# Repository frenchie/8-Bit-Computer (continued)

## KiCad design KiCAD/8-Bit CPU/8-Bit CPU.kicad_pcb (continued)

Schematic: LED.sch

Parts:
D96, D97, D98, D99, D100, D101, D102, D103: LED; LED_0805_2012Metric
RN31, RN32: 1k; R_Array_Concave_4x0603

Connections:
/Control/I0: RN31.5 (R4.2); also elsewhere on the board
/Control/I1: RN31.6 (R3.2); also elsewhere on the board
/Control/I2: RN31.7 (R2.2); also elsewhere on the board
/Control/I3: RN31.8 (R1.2); also elsewhere on the board
/Control/I4: RN32.5 (R4.2); also elsewhere on the board
/Control/I5: RN32.6 (R3.2); also elsewhere on the board
/Control/I6: RN32.7 (R2.2); also elsewhere on the board
/Control/I7: RN32.8 (R1.2); also elsewhere on the board
GND: D96.1 (K), D97.1 (K), D98.1 (K), D99.1 (K), D100.1 (K), D101.1 (K), D102.1 (K), D103.1 (K); also elsewhere on the board
unnamed: D96.2 (A), RN31.4 (R4.1)
unnamed: D97.2 (A), RN31.3 (R3.1)
unnamed: D98.2 (A), RN31.2 (R2.1)
unnamed: D99.2 (A), RN31.1 (R1.1)
unnamed: D100.2 (A), RN32.4 (R4.1)
unnamed: D101.2 (A), RN32.3 (R3.1)
unnamed: D102.2 (A), RN32.2 (R2.1)
unnamed: D103.2 (A), RN32.1 (R1.1)

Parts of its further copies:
D4, D5, D6, D7, D8, D9, D10, D11, D15, D16, D17, D18, D19, D20, D21, D22, D24, D25, D26, D27, D28, D29, D30, D31, D52, D53, D54, D55, D56, D57, D58, D59, D60, D61, D62, D63, D64, D65, D66, D67: LED; LED_0805_2012Metric
RN1, RN2, RN3, RN4, RN13, RN14, RN22, RN23, RN24, RN25: 1k; R_Array_Concave_4x0603

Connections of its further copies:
/ALU/B0: RN22.8 (R1.2); also elsewhere on the board
/ALU/B1: RN22.7 (R2.2); also elsewhere on the board
/ALU/B2: RN22.6 (R3.2); also elsewhere on the board
/ALU/B3: RN22.5 (R4.2); also elsewhere on the board
/ALU/B4: RN23.8 (R1.2); also elsewhere on the board
/ALU/B5: RN23.7 (R2.2); also elsewhere on the board
/ALU/B6: RN23.6 (R3.2); also elsewhere on the board
/ALU/B7: RN23.5 (R4.2); also elsewhere on the board
/ALU/PD0: RN24.8 (R1.2); also elsewhere on the board
/ALU/PD1: RN24.7 (R2.2); also elsewhere on the board
/ALU/PD2: RN24.6 (R3.2); also elsewhere on the board
/ALU/PD3: RN24.5 (R4.2); also elsewhere on the board
/ALU/PD4: RN25.8 (R1.2); also elsewhere on the board
/ALU/PD5: RN25.7 (R2.2); also elsewhere on the board
/ALU/PD6: RN25.6 (R3.2); also elsewhere on the board
/ALU/PD7: RN25.5 (R4.2); also elsewhere on the board
/Program Counter/PC0: RN1.8 (R1.2); also elsewhere on the board
/Program Counter/PC1: RN1.7 (R2.2); also elsewhere on the board
/Program Counter/PC2: RN1.6 (R3.2); also elsewhere on the board
/Program Counter/PC3: RN1.5 (R4.2); also elsewhere on the board
/Program Counter/PC4: RN2.8 (R1.2); also elsewhere on the board
/Program Counter/PC5: RN2.7 (R2.2); also elsewhere on the board
/Program Counter/PC6: RN2.6 (R3.2); also elsewhere on the board
/Program Counter/PC7: RN2.5 (R4.2); also elsewhere on the board
/RAM/MA0: RN3.8 (R1.2); also elsewhere on the board
/RAM/MA1: RN3.7 (R2.2); also elsewhere on the board
/RAM/MA2: RN3.6 (R3.2); also elsewhere on the board
/RAM/MA3: RN3.5 (R4.2); also elsewhere on the board
/RAM/MA4: RN4.8 (R1.2); also elsewhere on the board
/RAM/MA5: RN4.7 (R2.2); also elsewhere on the board
/RAM/MA6: RN4.6 (R3.2); also elsewhere on the board
/RAM/MA7: RN4.5 (R4.2); also elsewhere on the board
/RAM/RAM0: RN13.8 (R1.2); also elsewhere on the board
/RAM/RAM1: RN13.7 (R2.2); also elsewhere on the board
/RAM/RAM2: RN13.6 (R3.2); also elsewhere on the board
/RAM/RAM3: RN13.5 (R4.2); also elsewhere on the board
/RAM/RAM4: RN14.8 (R1.2); also elsewhere on the board
/RAM/RAM5: RN14.7 (R2.2); also elsewhere on the board
/RAM/RAM6: RN14.6 (R3.2); also elsewhere on the board
/RAM/RAM7: RN14.5 (R4.2); also elsewhere on the board
GND: D4.1 (K), D5.1 (K), D6.1 (K), D7.1 (K), D8.1 (K), D9.1 (K), D10.1 (K), D11.1 (K), D15.1 (K), D16.1 (K), D17.1 (K), D18.1 (K), D19.1 (K), D20.1 (K), D21.1 (K), D22.1 (K), D24.1 (K), D25.1 (K), D26.1 (K), D27.1 (K), D28.1 (K), D29.1 (K), D30.1 (K), D31.1 (K), D52.1 (K), D53.1 (K), D54.1 (K), D55.1 (K), D56.1 (K), D57.1 (K), D58.1 (K), D59.1 (K), D60.1 (K), D61.1 (K), D62.1 (K), D63.1 (K), D64.1 (K), D65.1 (K), D66.1 (K), D67.1 (K); also elsewhere on the board
unnamed: D4.2 (A), RN1.4 (R4.1)
unnamed: D5.2 (A), RN1.3 (R3.1)
unnamed: D6.2 (A), RN1.2 (R2.1)
unnamed: D7.2 (A), RN1.1 (R1.1)
unnamed: D8.2 (A), RN2.4 (R4.1)
unnamed: D9.2 (A), RN2.3 (R3.1)
unnamed: D10.2 (A), RN2.2 (R2.1)
unnamed: D11.2 (A), RN2.1 (R1.1)
unnamed: D15.2 (A), RN3.4 (R4.1)
unnamed: D16.2 (A), RN3.3 (R3.1)
unnamed: D17.2 (A), RN3.2 (R2.1)
unnamed: D18.2 (A), RN3.1 (R1.1)
unnamed: D19.2 (A), RN4.4 (R4.1)
unnamed: D20.2 (A), RN4.3 (R3.1)
unnamed: D21.2 (A), RN4.2 (R2.1)
unnamed: D22.2 (A), RN4.1 (R1.1)
unnamed: D24.2 (A), RN13.4 (R4.1)
unnamed: D25.2 (A), RN13.3 (R3.1)
unnamed: D26.2 (A), RN13.2 (R2.1)
unnamed: D27.2 (A), RN13.1 (R1.1)
unnamed: D28.2 (A), RN14.4 (R4.1)
unnamed: D29.2 (A), RN14.3 (R3.1)
unnamed: D30.2 (A), RN14.2 (R2.1)
unnamed: D31.2 (A), RN14.1 (R1.1)
unnamed: D52.2 (A), RN22.4 (R4.1)
unnamed: D53.2 (A), RN22.3 (R3.1)
unnamed: D54.2 (A), RN22.2 (R2.1)
unnamed: D55.2 (A), RN22.1 (R1.1)
unnamed: D56.2 (A), RN23.4 (R4.1)
unnamed: D57.2 (A), RN23.3 (R3.1)
unnamed: D58.2 (A), RN23.2 (R2.1)
unnamed: D59.2 (A), RN23.1 (R1.1)
unnamed: D60.2 (A), RN24.4 (R4.1)
unnamed: D61.2 (A), RN24.3 (R3.1)
unnamed: D62.2 (A), RN24.2 (R2.1)
unnamed: D63.2 (A), RN24.1 (R1.1)
unnamed: D64.2 (A), RN25.4 (R4.1)
unnamed: D65.2 (A), RN25.3 (R3.1)
unnamed: D66.2 (A), RN25.2 (R2.1)
unnamed: D67.2 (A), RN25.1 (R1.1)

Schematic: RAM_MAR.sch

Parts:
C6, C7, C8: 100n; C_0805_2012Metric
D23: LED; LED_0805_2012Metric
R8: 1k; R_0805_2012Metric
RN5, RN6: 10k; R_Array_Concave_4x0603
SW2: SW_DIP_x08; SW_DIP_SPSTx08_Slide_9.78x22.5mm_W7.62mm_P2.54mm
U6: 74HC377; SOIC-20W_7.5x12.8mm_P1.27mm_Rounded
U7, U8: 74HC157; SOIC-16_3.9x9.9mm_P1.27mm_JCF

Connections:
/BUS0: U6.13 (D4); also elsewhere on the board
/BUS1: U6.14 (D5); also elsewhere on the board
/BUS2: U6.8 (D3); also elsewhere on the board
/BUS3: U6.7 (D2); also elsewhere on the board
/BUS4: U6.17 (D6); also elsewhere on the board
/BUS5: U6.4 (D1); also elsewhere on the board
/BUS6: U6.18 (D7); also elsewhere on the board
/BUS7: U6.3 (D0); also elsewhere on the board
/CLK: U6.11 (CP); also elsewhere on the board
/RAM/AddrReg/D0A: U6.12 (Q4), U7.2 (I0a)
/RAM/AddrReg/D0B: RN6.5 (R4.2), SW2.9, U7.3 (I1a)
/RAM/AddrReg/D1A: U6.15 (Q5), U7.14 (I0d)
/RAM/AddrReg/D1B: RN6.6 (R3.2), SW2.10, U7.13 (I1d)
/RAM/AddrReg/D2A: U6.9 (Q3), U7.5 (I0b)
/RAM/AddrReg/D2B: RN6.7 (R2.2), SW2.11, U7.6 (I1b)
/RAM/AddrReg/D3A: U6.6 (Q2), U7.11 (I0c)
/RAM/AddrReg/D3B: RN6.8 (R1.2), SW2.12, U7.10 (I1c)
/RAM/AddrReg/D4A: U6.16 (Q6), U8.2 (I0a)
/RAM/AddrReg/D4B: RN5.5 (R4.2), SW2.13, U8.3 (I1a)
/RAM/AddrReg/D5A: U6.5 (Q1), U8.14 (I0d)
/RAM/AddrReg/D5B: RN5.6 (R3.2), SW2.14, U8.13 (I1d)
/RAM/AddrReg/D6A: U6.19 (Q7), U8.5 (I0b)
/RAM/AddrReg/D6B: RN5.7 (R2.2), SW2.15, U8.6 (I1b)
/RAM/AddrReg/D7A: U6.2 (Q0), U8.11 (I0c)
/RAM/AddrReg/D7B: RN5.8 (R1.2), SW2.16, U8.10 (I1c)
/RAM/MA0: U7.4 (Za); also elsewhere on the board
/RAM/MA1: U7.12 (Zd); also elsewhere on the board
/RAM/MA2: U7.7 (Zb); also elsewhere on the board
/RAM/MA3: U7.9 (Zc); also elsewhere on the board
/RAM/MA4: U8.4 (Za); also elsewhere on the board
/RAM/MA5: U8.12 (Zd); also elsewhere on the board
/RAM/MA6: U8.7 (Zb); also elsewhere on the board
/RAM/MA7: U8.9 (Zc); also elsewhere on the board
/RAM/MAN: U7.1 (S), U8.1 (S); also elsewhere on the board
/~MI: D23.1 (K), U6.1 (~E); also elsewhere on the board
GND: C6.2, C7.2, C8.2, RN5.1 (R1.1), RN5.2 (R2.1), RN5.3 (R3.1), RN5.4 (R4.1), RN6.1 (R1.1), RN6.2 (R2.1), RN6.3 (R3.1), RN6.4 (R4.1), U6.10 (GND), U7.8 (GND), U7.15 (E), U8.8 (GND), U8.15 (E); also elsewhere on the board
unnamed: D23.2 (A), R8.1
VCC: C6.1, C7.1, C8.1, R8.2, SW2.1, SW2.2, SW2.3, SW2.4, SW2.5, SW2.6, SW2.7, SW2.8, U6.20 (VCC), U7.16 (VCC), U8.16 (VCC); also elsewhere on the board

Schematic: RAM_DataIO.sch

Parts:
C9, C10, C11: 100n; C_0805_2012Metric
RN7, RN8, RN9, RN10, RN11, RN12: 10k; R_Array_Concave_4x0603
SW3: SW_DIP_x08; SW_DIP_SPSTx08_Slide_9.78x22.5mm_W7.62mm_P2.54mm
U9, U10, U11: 74HC245; SOIC-20W_7.5x12.8mm_P1.27mm

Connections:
/BUS0: U9.11 (B7), U11.11 (B7); also elsewhere on the board
/BUS1: U9.12 (B6), U11.12 (B6); also elsewhere on the board
/BUS2: U9.13 (B5), U11.13 (B5); also elsewhere on the board
/BUS3: U9.14 (B4), U11.14 (B4); also elsewhere on the board
/BUS4: U9.15 (B3), U11.15 (B3); also elsewhere on the board
/BUS5: U9.16 (B2), U11.16 (B2); also elsewhere on the board
/BUS6: U9.17 (B1), U11.17 (B1); also elsewhere on the board
/BUS7: U9.18 (B0), U11.18 (B0); also elsewhere on the board
/RAM/Data IO/D0: RN12.5 (R4.2), U10.9 (A7)
/RAM/Data IO/D0A: RN9.1 (R1.1), U9.9 (A7), U10.11 (B7)
/RAM/Data IO/D0B: RN7.1 (R1.1), RN9.8 (R1.2), SW3.9
/RAM/Data IO/D1: RN12.6 (R3.2), U10.8 (A6)
/RAM/Data IO/D1A: RN9.2 (R2.1), U9.8 (A6), U10.12 (B6)
/RAM/Data IO/D1B: RN7.2 (R2.1), RN9.7 (R2.2), SW3.10
/RAM/Data IO/D2: RN12.7 (R2.2), U10.7 (A5)
/RAM/Data IO/D2A: RN9.3 (R3.1), U9.7 (A5), U10.13 (B5)
/RAM/Data IO/D2B: RN7.3 (R3.1), RN9.6 (R3.2), SW3.11
/RAM/Data IO/D3: RN12.8 (R1.2), U10.6 (A4)
/RAM/Data IO/D3A: RN9.4 (R4.1), U9.6 (A4), U10.14 (B4)
/RAM/Data IO/D3B: RN7.4 (R4.1), RN9.5 (R4.2), SW3.12
/RAM/Data IO/D4: RN11.5 (R4.2), U10.5 (A3)
/RAM/Data IO/D4A: RN10.1 (R1.1), U9.5 (A3), U10.15 (B3)
/RAM/Data IO/D4B: RN8.1 (R1.1), RN10.8 (R1.2), SW3.13
/RAM/Data IO/D5: RN11.6 (R3.2), U10.4 (A2)
/RAM/Data IO/D5A: RN10.2 (R2.1), U9.4 (A2), U10.16 (B2)
/RAM/Data IO/D5B: RN8.2 (R2.1), RN10.7 (R2.2), SW3.14
/RAM/Data IO/D6: RN11.7 (R2.2), U10.3 (A1)
/RAM/Data IO/D6A: RN10.3 (R3.1), U9.3 (A1), U10.17 (B1)
/RAM/Data IO/D6B: RN8.3 (R3.1), RN10.6 (R3.2), SW3.15
/RAM/Data IO/D7: RN11.8 (R1.2), U10.2 (A0)
/RAM/Data IO/D7A: RN10.4 (R4.1), U9.2 (A0), U10.18 (B0)
/RAM/Data IO/D7B: RN8.4 (R4.1), RN10.5 (R4.2), SW3.16
/RAM/MAN: U9.19 (CE); also elsewhere on the board
/RAM/RAM0: RN12.4 (R4.1), U11.9 (A7); also elsewhere on the board
/RAM/RAM1: RN12.3 (R3.1), U11.8 (A6); also elsewhere on the board
/RAM/RAM2: RN12.2 (R2.1), U11.7 (A5); also elsewhere on the board
/RAM/RAM3: RN12.1 (R1.1), U11.6 (A4); also elsewhere on the board
/RAM/RAM4: RN11.4 (R4.1), U11.5 (A3); also elsewhere on the board
/RAM/RAM5: RN11.3 (R3.1), U11.4 (A2); also elsewhere on the board
/RAM/RAM6: RN11.2 (R2.1), U11.3 (A1); also elsewhere on the board
/RAM/RAM7: RN11.1 (R1.1), U11.2 (A0); also elsewhere on the board
/~RO: U11.19 (CE); also elsewhere on the board
GND: C9.2, C10.2, C11.2, RN7.5 (R4.2), RN7.6 (R3.2), RN7.7 (R2.2), RN7.8 (R1.2), RN8.5 (R4.2), RN8.6 (R3.2), RN8.7 (R2.2), RN8.8 (R1.2), U9.1 (A->B), U9.10 (GND), U10.1 (A->B), U10.10 (GND), U10.19 (CE), U11.10 (GND); also elsewhere on the board
VCC: C9.1, C10.1, C11.1, SW3.1, SW3.2, SW3.3, SW3.4, SW3.5, SW3.6, SW3.7, SW3.8, U9.20 (VCC), U10.20 (VCC), U11.1 (A->B), U11.20 (VCC); also elsewhere on the board

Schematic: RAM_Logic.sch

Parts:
C12, C13: 1u; C_0805_2012Metric
C14: 47n; C_0805_2012Metric
C15, C16: 100n; C_0805_2012Metric
D32: GREEN; LED_0805_2012Metric
D33: RED; LED_0805_2012Metric
R9, R12, R13: 10k; R_0805_2012Metric
R10: 4k7; R_0805_2012Metric
R11, R15: 1k; R_0805_2012Metric
R14: 220k; R_0805_2012Metric
SW4, SW5: SW_Push; SW_TH_Tactile_Omron_B3F-10xx_Fixed
U12: 74HC00; SOIC-14_3.9x8.7mm_P1.27mm_JCF
U13: 74HC132; SOIC-14_3.9x8.7mm_P1.27mm_JCF

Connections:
/CLK: U12.5; also elsewhere on the board
/RAM/MAN: D33.2 (A), R11.1, U12.8, U13.1, U13.12; also elsewhere on the board
/RAM/~WR: U13.8; also elsewhere on the board
/~RI: U12.1, U12.2; also elsewhere on the board
GND: C13.2, C14.2, C15.2, C16.2, R10.1, R15.1, SW4.1, U12.7 (GND), U13.7 (GND); also elsewhere on the board
unnamed: C12.1, U13.6
unnamed: C12.2, R9.2, R10.2
unnamed: C13.1, R13.1, U13.13
unnamed: C14.1, R14.1, SW5.1
unnamed: D32.1 (K), D33.1 (K), R15.2
unnamed: D32.2 (A), R14.2, U12.9, U12.10, U12.11
unnamed: R9.1, U13.9, U13.10
unnamed: R11.2, SW5.2, U12.12, U12.13
unnamed: R12.1, R13.2, SW4.2
unnamed: U12.3, U12.4
unnamed: U12.6, U13.5
unnamed: U13.3, U13.4
unnamed: U13.2, U13.11
VCC: C15.1, C16.1, R12.2, U12.14 (VCC), U13.14 (VCC); also elsewhere on the board

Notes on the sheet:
Local / Remote Programming
Write Control: Turns the Clock or Push Button into a 3 ms low going pulse. Logic gates out whichever circuit is not currently in use.

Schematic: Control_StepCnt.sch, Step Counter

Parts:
C37: 100n; C_0805_2012Metric
D88, D89, D90: LED; LED_0805_2012Metric
RN30: 1k; R_Array_Concave_4x0603
U30: 74HC161; SOIC-16_3.9x9.9mm_P1.27mm

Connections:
/Control/S0: D88.2 (A), U30.14 (Q0); also elsewhere on the board
/Control/S1: D89.2 (A), U30.13 (Q1); also elsewhere on the board
/Control/S2: D90.2 (A), U30.12 (Q2); also elsewhere on the board
/Control/~MSR: U30.9 (~PE); also elsewhere on the board
/Control/~RESET: U30.1 (~MR); also elsewhere on the board
/~CLK: U30.2 (CP); also elsewhere on the board
GND: C37.2, RN30.5 (R4.2), RN30.6 (R3.2), RN30.7 (R2.2), U30.3 (D0), U30.4 (D1), U30.5 (D2), U30.6 (D3), U30.8 (GND); also elsewhere on the board
unnamed: D88.1 (K), RN30.4 (R4.1)
unnamed: D89.1 (K), RN30.3 (R3.1)
unnamed: D90.1 (K), RN30.2 (R2.1)
VCC: C37.1, U30.7 (CEP), U30.10 (CET), U30.16 (VCC); also elsewhere on the board

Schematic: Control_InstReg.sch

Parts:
C38: 100n; C_0805_2012Metric
D91: LED; LED_0805_2012Metric
R27: 1k; R_0805_2012Metric
U31: 74HC377; SOIC-20W_7.5x12.8mm_P1.27mm

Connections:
/BUS0: U31.13 (D4); also elsewhere on the board
/BUS1: U31.8 (D3); also elsewhere on the board
/BUS2: U31.7 (D2); also elsewhere on the board
/BUS3: U31.14 (D5); also elsewhere on the board
/BUS4: U31.4 (D1); also elsewhere on the board
/BUS5: U31.17 (D6); also elsewhere on the board
/BUS6: U31.3 (D0); also elsewhere on the board
/BUS7: U31.18 (D7); also elsewhere on the board
/CLK: U31.11 (CP); also elsewhere on the board
/Control/I0: U31.12 (Q4); also elsewhere on the board
/Control/I1: U31.9 (Q3); also elsewhere on the board
/Control/I2: U31.6 (Q2); also elsewhere on the board
/Control/I3: U31.15 (Q5); also elsewhere on the board
/Control/I4: U31.5 (Q1); also elsewhere on the board
/Control/I5: U31.16 (Q6); also elsewhere on the board
/Control/I6: U31.2 (Q0); also elsewhere on the board
/Control/I7: U31.19 (Q7); also elsewhere on the board
/Control/~IRI: R27.1, U31.1 (~E); also elsewhere on the board
GND: C38.2, U31.10 (GND); also elsewhere on the board
unnamed: D91.1 (K), R27.2
VCC: C38.1, D91.2 (A), U31.20 (VCC); also elsewhere on the board

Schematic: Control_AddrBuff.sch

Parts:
C39, C40: 100n; C_0805_2012Metric
U32, U33: 74HC245; SOIC-20W_7.5x12.8mm_P1.27mm

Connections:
/CRY: U33.17 (B1); also elsewhere on the board
/Control/A0: U32.18 (B0); also elsewhere on the board
/Control/A1: U32.17 (B1); also elsewhere on the board
/Control/A2: U32.16 (B2); also elsewhere on the board
/Control/A3: U32.15 (B3); also elsewhere on the board
/Control/A4: U32.14 (B4); also elsewhere on the board
/Control/A5: U32.13 (B5); also elsewhere on the board
/Control/A6: U32.12 (B6); also elsewhere on the board
/Control/A7: U32.11 (B7); also elsewhere on the board
/Control/A8: U33.6 (A4); also elsewhere on the board
/Control/A9: U33.5 (A3); also elsewhere on the board
/Control/A10: U33.4 (A2); also elsewhere on the board
/Control/A11: U33.3 (A1); also elsewhere on the board
/Control/A12: U33.2 (A0); also elsewhere on the board
/Control/FL: U33.18 (B0); also elsewhere on the board
/Control/I0: U32.2 (A0); also elsewhere on the board
/Control/I1: U32.3 (A1); also elsewhere on the board
/Control/I2: U32.4 (A2); also elsewhere on the board
/Control/I3: U32.5 (A3); also elsewhere on the board
/Control/I4: U32.6 (A4); also elsewhere on the board
/Control/I5: U32.7 (A5); also elsewhere on the board
/Control/I6: U32.8 (A6); also elsewhere on the board
/Control/I7: U32.9 (A7); also elsewhere on the board
/Control/S0: U33.14 (B4); also elsewhere on the board
/Control/S1: U33.15 (B3); also elsewhere on the board
/Control/S2: U33.16 (B2); also elsewhere on the board
/Control/~AE: U32.19 (CE), U33.19 (CE); also elsewhere on the board
GND: C39.2, C40.2, U32.10 (GND), U33.1 (A->B), U33.10 (GND), U33.11 (B7), U33.12 (B6), U33.13 (B5); also elsewhere on the board
VCC: C39.1, C40.1, U32.1 (A->B), U32.20 (VCC), U33.20 (VCC); also elsewhere on the board

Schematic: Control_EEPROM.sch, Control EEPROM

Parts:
C44, C45, C46: 100n; C_0805_2012Metric
D93: LED; LED_0805_2012Metric
R30: 1k; R_0805_2012Metric
R31: 10k; R_0805_2012Metric
U38: 28C64B; SOIC-28W_7.5x17.9mm_P1.27mm
U39, U40: 74HC1G00; TSOP-5_1.65x3.05mm_P0.95mm
U41: 74HC245; SOIC-20W_7.5x12.8mm_P1.27mm

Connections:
/Control/A0: U38.10 (A0); also elsewhere on the board
/Control/A1: U38.9 (A1); also elsewhere on the board
/Control/A2: U38.21 (A10); also elsewhere on the board
/Control/A3: U38.8 (A2); also elsewhere on the board
/Control/A4: U38.7 (A3); also elsewhere on the board
/Control/A5: U38.23 (A11); also elsewhere on the board
/Control/A6: U38.6 (A4); also elsewhere on the board
/Control/A7: U38.24 (A9); also elsewhere on the board
/Control/A8: U38.2 (A12); also elsewhere on the board
/Control/A9: U38.3 (A7); also elsewhere on the board
/Control/A10: U38.4 (A6); also elsewhere on the board
/Control/A11: U38.25 (A8); also elsewhere on the board
/Control/A12: U38.5 (A5); also elsewhere on the board
/Control/D0: U41.2 (A0); also elsewhere on the board
/Control/D1: U41.3 (A1); also elsewhere on the board
/Control/D2: U41.4 (A2); also elsewhere on the board
/Control/D3: U41.5 (A3); also elsewhere on the board
/Control/D4: U41.6 (A4); also elsewhere on the board
/Control/D5: U41.7 (A5); also elsewhere on the board
/Control/D6: U41.8 (A6); also elsewhere on the board
/Control/D7: U41.9 (A7); also elsewhere on the board
/Control/DIR: U41.1 (A->B); also elsewhere on the board
/Control/EEPROM 1/~WR: U38.27 (~WE), U39.4
/Control/WR: U39.1; also elsewhere on the board
/Control/~AS: D93.1 (K), R31.2, U40.1, U40.2, U41.19 (CE); also elsewhere on the board
/Control/~EE: U38.22 (~OE); also elsewhere on the board
/~CI: U38.19 (IO7), U41.15 (B3); also elsewhere on the board
/~CO: U38.11 (IO0), U41.16 (B2); also elsewhere on the board
/~SPI: U38.13 (IO2), U41.18 (B0); also elsewhere on the board
/~SPO: U38.12 (IO1), U41.17 (B1); also elsewhere on the board
/Σ0: U38.18 (IO6), U41.14 (B4); also elsewhere on the board
/Σ1: U38.17 (IO5), U41.13 (B5); also elsewhere on the board
/Σ2: U38.16 (IO4), U41.12 (B6); also elsewhere on the board
/Σ3: U38.15 (IO3), U41.11 (B7); also elsewhere on the board
GND: C44.2, C45.2, C46.2, U38.14 (GND), U38.20 (~CE), U39.3 (GND), U40.3 (GND), U41.10 (GND); also elsewhere on the board
unnamed: D93.2 (A), R30.2
unnamed: U39.2, U40.4
VCC: C44.1, C45.1, C46.1, R30.1, R31.1, U38.28 (VCC), U39.5 (VCC), U40.5 (VCC), U41.20 (VCC); also elsewhere on the board

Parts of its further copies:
C41, C42, C43, C52, C53, C54: 100n; C_0805_2012Metric
D92, D95: LED; LED_0805_2012Metric
R28, R39: 1k; R_0805_2012Metric
R29, R40: 10k; R_0805_2012Metric
U34, U44: 28C64B; SOIC-28W_7.5x17.9mm_P1.27mm
U35, U36, U45, U46: 74HC1G00; TSOP-5_1.65x3.05mm_P0.95mm
U37, U47: 74HC245; SOIC-20W_7.5x12.8mm_P1.27mm

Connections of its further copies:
/Control/A0: U34.10 (A0), U44.10 (A0); also elsewhere on the board
/Control/A1: U34.9 (A1), U44.9 (A1); also elsewhere on the board
/Control/A2: U34.21 (A10), U44.21 (A10); also elsewhere on the board
/Control/A3: U34.8 (A2), U44.8 (A2); also elsewhere on the board
/Control/A4: U34.7 (A3), U44.7 (A3); also elsewhere on the board
/Control/A5: U34.23 (A11), U44.23 (A11); also elsewhere on the board
/Control/A6: U34.6 (A4), U44.6 (A4); also elsewhere on the board
/Control/A7: U34.24 (A9), U44.24 (A9); also elsewhere on the board
/Control/A8: U34.2 (A12), U44.2 (A12); also elsewhere on the board
/Control/A9: U34.3 (A7), U44.3 (A7); also elsewhere on the board
/Control/A10: U34.4 (A6), U44.4 (A6); also elsewhere on the board
/Control/A11: U34.25 (A8), U44.25 (A8); also elsewhere on the board
/Control/A12: U34.5 (A5), U44.5 (A5); also elsewhere on the board
/Control/D0: U37.2 (A0), U47.2 (A0); also elsewhere on the board
/Control/D1: U37.3 (A1), U47.3 (A1); also elsewhere on the board
/Control/D2: U37.4 (A2), U47.4 (A2); also elsewhere on the board
/Control/D3: U37.5 (A3), U47.5 (A3); also elsewhere on the board
/Control/D4: U37.6 (A4), U47.6 (A4); also elsewhere on the board
/Control/D5: U37.7 (A5), U47.7 (A5); also elsewhere on the board
/Control/D6: U37.8 (A6), U47.8 (A6); also elsewhere on the board
/Control/D7: U37.9 (A7), U47.9 (A7); also elsewhere on the board
/Control/DIR: U37.1 (A->B), U47.1 (A->B); also elsewhere on the board
/Control/EEPROM 2/~WR: U34.27 (~WE), U35.4
/Control/EEPROM 3/~WR: U44.27 (~WE), U45.4
/Control/WR: U35.1, U45.1; also elsewhere on the board
/Control/~BS: D92.1 (K), R29.2, U36.1, U36.2, U37.19 (CE); also elsewhere on the board
/Control/~CS: D95.1 (K), R40.2, U46.1, U46.2, U47.19 (CE); also elsewhere on the board
/Control/~EE: U34.22 (~OE), U44.22 (~OE); also elsewhere on the board
/Control/~IRI: U44.15 (IO3), U47.11 (B7); also elsewhere on the board
/Control/~MSR: U44.16 (IO4), U47.12 (B6); also elsewhere on the board
/MP: U34.18 (IO6), U37.14 (B4); also elsewhere on the board
/PE: U44.19 (IO7), U47.15 (B3); also elsewhere on the board
/~AI: U44.12 (IO1), U47.17 (B1); also elsewhere on the board
/~AO: U44.13 (IO2), U47.18 (B0); also elsewhere on the board
/~BI: U34.15 (IO3), U37.11 (B7); also elsewhere on the board
/~BO: U34.16 (IO4), U37.12 (B6); also elsewhere on the board
/~HLT: U44.11 (IO0), U47.16 (B2); also elsewhere on the board
/~MI: U34.17 (IO5), U37.13 (B5); also elsewhere on the board
/~PI: U44.17 (IO5), U47.13 (B5); also elsewhere on the board
/~PO: U44.18 (IO6), U47.14 (B4); also elsewhere on the board
/~RI: U34.11 (IO0), U37.16 (B2); also elsewhere on the board
/~RO: U34.19 (IO7), U37.15 (B3); also elsewhere on the board
/~ΣI: U34.12 (IO1), U37.17 (B1); also elsewhere on the board
/~ΣO: U34.13 (IO2), U37.18 (B0); also elsewhere on the board
GND: C41.2, C42.2, C43.2, C52.2, C53.2, C54.2, U34.14 (GND), U34.20 (~CE), U35.3 (GND), U36.3 (GND), U37.10 (GND), U44.14 (GND), U44.20 (~CE), U45.3 (GND), U46.3 (GND), U47.10 (GND); also elsewhere on the board
unnamed: D92.2 (A), R28.2
unnamed: D95.2 (A), R39.2
unnamed: U35.2, U36.4
unnamed: U45.2, U46.4
VCC: C41.1, C42.1, C43.1, C52.1, C53.1, C54.1, R28.1, R29.1, R39.1, R40.1, U34.28 (VCC), U35.5 (VCC), U36.5 (VCC), U37.20 (VCC), U44.28 (VCC), U45.5 (VCC), U46.5 (VCC), U47.20 (VCC); also elsewhere on the board

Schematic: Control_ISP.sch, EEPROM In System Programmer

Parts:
C47, C48, C49, C50, C51: 100n; C_0805_2012Metric
D94: LED; LED_0805_2012Metric
J3: I2C; PinHeader_1x04_P2.54mm_Vertical
J4: AVRISP; PinHeader_2x03_P2.54mm_Vertical
R32, R33: 3k3; R_0805_2012Metric
R34, R35, R37, R38: 10k; R_0805_2012Metric
R36: 1k; R_0805_2012Metric
U42: CAT24C256; SOIC-8_3.9x4.9mm_P1.27mm
U43: ATmega16-16AU; TQFP-44_10x10mm_P0.8mm

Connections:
/Control/A0: U43.9 (PD0); also elsewhere on the board
/Control/A1: U43.10 (PD1); also elsewhere on the board
/Control/A2: U43.11 (PD2); also elsewhere on the board
/Control/A3: U43.12 (PD3); also elsewhere on the board
/Control/A4: U43.13 (PD4); also elsewhere on the board
/Control/A5: U43.14 (PD5); also elsewhere on the board
/Control/A6: U43.15 (PD6); also elsewhere on the board
/Control/A7: U43.16 (PD7); also elsewhere on the board
/Control/A8: U43.40 (PB0); also elsewhere on the board
/Control/A9: U43.41 (PB1); also elsewhere on the board
/Control/A10: U43.42 (PB2); also elsewhere on the board
/Control/A11: U43.43 (PB3); also elsewhere on the board
/Control/A12: U43.44 (PB4); also elsewhere on the board
/Control/D0: U43.37 (PA0); also elsewhere on the board
/Control/D1: U43.36 (PA1); also elsewhere on the board
/Control/D2: U43.35 (PA2); also elsewhere on the board
/Control/D3: U43.34 (PA3); also elsewhere on the board
/Control/D4: U43.33 (PA4); also elsewhere on the board
/Control/D5: U43.32 (PA5); also elsewhere on the board
/Control/D6: U43.31 (PA6); also elsewhere on the board
/Control/D7: U43.30 (PA7); also elsewhere on the board
/Control/DIR: R35.2, U43.22 (PC3); also elsewhere on the board
/Control/Programmer/MISO: J4.1, U43.2 (PB6)
/Control/Programmer/SCK: J4.3, U43.3 (PB7)
/Control/Programmer/SCL: J3.3, R33.1, U42.6 (SCL), U43.19 (PC0)
/Control/Programmer/SDA: J3.2, R32.1, U42.5 (SDA), U43.20 (PC1)
/Control/Programmer/~RST: J4.5, R34.2, U43.4 (~RESET)
/Control/WR: J4.4, U43.1 (PB5); also elsewhere on the board
/Control/~AE: R37.1, U43.21 (PC2); also elsewhere on the board
/Control/~AS: U43.23 (PC4); also elsewhere on the board
/Control/~BS: U43.24 (PC5); also elsewhere on the board
/Control/~CS: U43.25 (PC6); also elsewhere on the board
/Control/~EE: R36.2, R38.1, U43.26 (PC7); also elsewhere on the board
GND: C47.2, C48.2, C49.2, C50.2, C51.2, D94.1 (K), J3.4, J4.6, R37.2, R38.2, U42.1 (A0), U42.2 (A1), U42.3 (A2), U42.4 (GND), U42.7 (WP), U43.6 (GND), U43.18 (GND), U43.28 (GND), U43.39 (GND); also elsewhere on the board
unnamed: D94.2 (A), R36.1
VCC: C47.1, C48.1, C49.1, C50.1, C51.1, J3.1, J4.2, R32.2, R33.2, R34.1, R35.1, U42.8 (VCC), U43.5 (VCC), U43.17 (VCC), U43.27 (AVCC), U43.38 (VCC); also elsewhere on the board

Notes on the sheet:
Signals Summary: ~AE~: Address Buffer Enable Output ~EE~: EEPROM Enable Output ~AS~: EEPROM A Select ~BS~: EEPROM B Select ~CS~: EEPROM C Select DIR: ~Read~/Write WR: Write (Pulse only)

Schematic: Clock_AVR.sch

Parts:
C64: 100n; C_0805_2012Metric
J6: AVRISP; PinHeader_2x03_P2.54mm_Vertical
RN33: 10k; R_Array_Concave_4x0603
RV1: 50k; BOURNS-3310Y
U53: ATtiny45-20SU; SOIC-8_5.275x5.275mm_P1.27mm

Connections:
/Clock/AVR: RN33.4 (R4.1); also elsewhere on the board
/Clock/AVR Clock/CLK: U53.3 (XTAL2/PB4); also elsewhere on the board
/Clock/AVR Clock/MISO: J6.1, RN33.6 (R3.2), U53.6 (PB1)
/Clock/AVR Clock/MOSI: J6.4, RN33.5 (R4.2), U53.5 (AREF/PB0)
/Clock/AVR Clock/SCK: J6.3, U53.7 (PB2)
/Clock/AVR Clock/~RESET: J6.5, RN33.8 (R1.2), U53.1 (~RESET~/PB5)
/~HLT: RN33.2 (R2.1), RN33.3 (R3.1); also elsewhere on the board
GND: C64.2, J6.6, RV1.3, U53.4 (GND); also elsewhere on the board
unnamed: RV1.2, U53.2 (XTAL1/PB3)
VCC: C64.1, J6.2, RN33.1 (R1.1), RN33.7 (R2.2), RV1.1, U53.8 (VCC); also elsewhere on the board

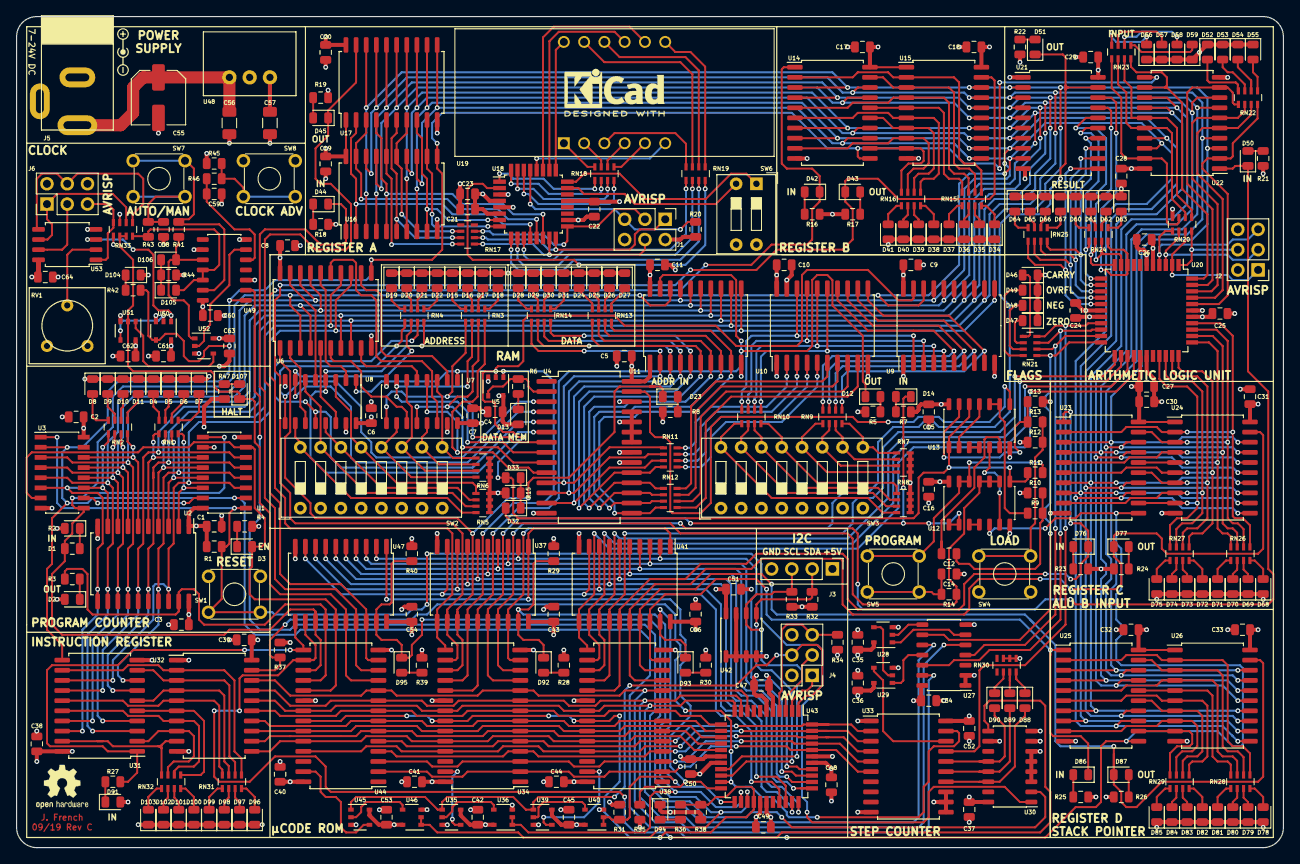
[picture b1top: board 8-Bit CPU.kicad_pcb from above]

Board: 4 copper layers, 158.8 x 104.1 mm, 320 parts (0 on the bottom side), 375 nets.

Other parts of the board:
svg2mod: G***; Polarity_marking_center_positive_1.5mm_FrontS

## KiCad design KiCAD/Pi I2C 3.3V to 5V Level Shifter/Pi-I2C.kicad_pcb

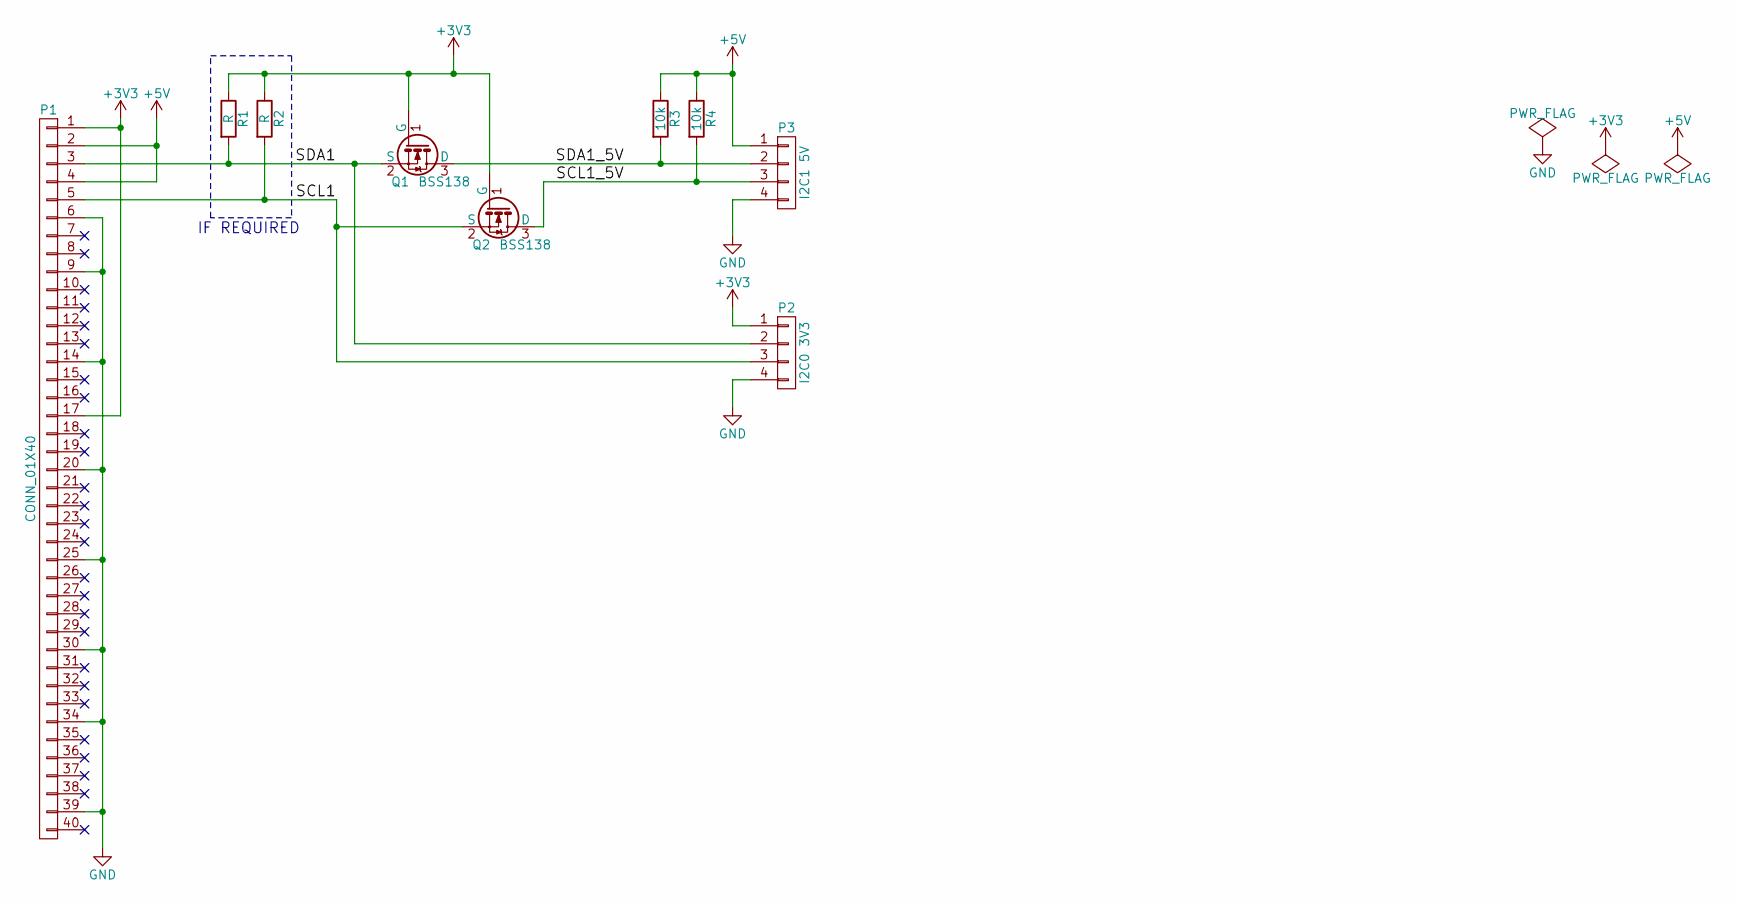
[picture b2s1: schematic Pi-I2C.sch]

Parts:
P1: CONN_01X40; Pin_Header_Straight_2x20
P2: I2C0 3V3; Pin_Header_Straight_1x04
P3: I2C1 5V; Pin_Header_Straight_1x04
Q1, Q2: BSS138; SOT-23
R1, R2: R; R_0805
R3, R4: 10k; R_0805

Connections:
+3V3: P1.1, P1.17, P2.1, Q1.1 (G), Q2.1 (G), R1.1, R2.1
+5V: P1.2, P1.4, P3.1, R3.1, R4.1
/SCL1: P1.5, P2.3, Q2.2 (S), R2.2
/SCL1_5V: P3.3, Q2.3 (D), R4.2
/SDA1: P1.3, P2.2, Q1.2 (S), R1.2
/SDA1_5V: P3.2, Q1.3 (D), R3.2
GND: P1.6, P1.9, P1.14, P1.20, P1.25, P1.30, P1.34, P1.39, P2.4, P3.4

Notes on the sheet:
IF REQUIRED

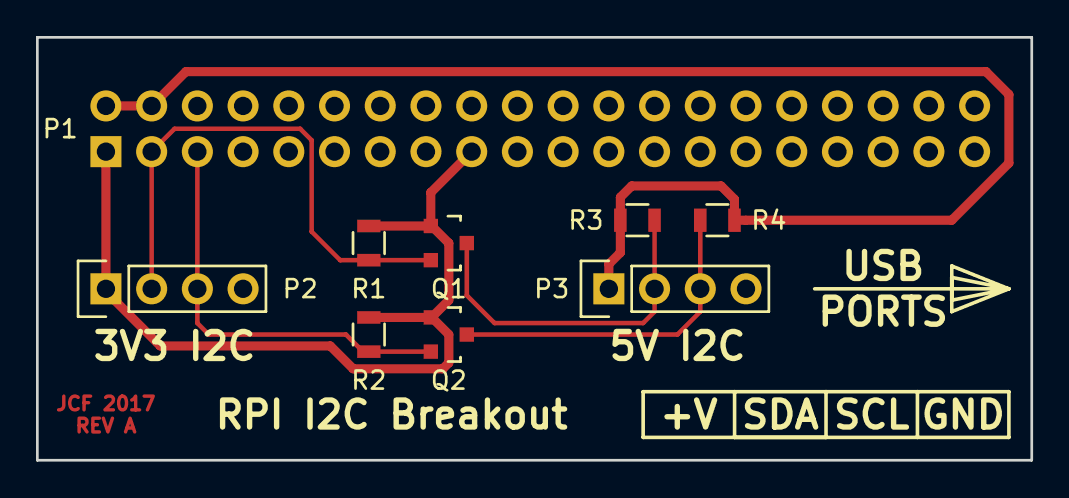
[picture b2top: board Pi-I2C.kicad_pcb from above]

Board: 2 copper layers, 55.2 x 23.5 mm, 9 parts (1 on the bottom side), 7 nets.

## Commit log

2019-08-23 8-Bit Computer Schematic Files,
    * Revision A - Untested Use at Own Risk
    * Pi I2C level shifter design
2019-09-01 Microcode for Rev A Board
    * Don't build the RevA board there are some issues!
2019-09-01 AVR Code for 7-Segment Display
    * ATMega48P
    * This works a treat!
2019-09-01 AVR Clock
    * Fits in an ATTiny25, uses an ATTiny45
2019-09-01 ALU
    * ATMega16
    * Not fuly tested yet
2019-09-01 Whitespace cleanup
2019-09-02 KiCAD cleanup - Revision A
    Revision A Known Issues:
    * ATTiny45 has incorrect footprint
    * Flags register is redundant (The ATMega16's output port is a register)
    * Power jack pinout is wrong (12V shorted to ground)
    * Step counter reset logic is wrong (Active high signalling, Active low input)
    * ALU output indicator not connected
2019-09-02 Deleted redundant schematic
2020-07-13 AVR Programmer, Manual & Licensing Cleanup
2020-07-13 7 Segment Licensing & Update
2020-07-13 In System Programmer Cleanup
2020-07-13 Update AVR Code to Latest Revision
2020-07-13 Readme Formatting
2020-07-13 Microcode Licensing & Tools
2020-07-13 KiCAD files update & Gerbers
2020-07-13 Block Diagrams
2020-07-13 Add arm.bin
2020-07-15 Accidentally committed a WIP Feature
